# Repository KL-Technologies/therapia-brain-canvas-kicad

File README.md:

# brain_canvas_kicad

Brain Canvas Rev.A (Therapia EEG/HRV board) を **EasyEDA Pro から KiCad 10 へ移行**し、
以後のレイアウト修理・製造データ出力を KiCad 側でヘッドレスに回すためのパイプライン。

対象基板: 4層 / 61.8236 × 45.0088 mm (2434 × 1772 mil) / 部品 131 個・全数 Top 実装。

## 前提

| 名前 | パス | 用途 |
|---|---|---|
| `KC` | `/Applications/KiCad/KiCad.app/Contents/MacOS/kicad-cli` | DRC・Gerber 等の CLI（10.0.5） |
| `KPY` | `/Applications/KiCad/KiCad.app/Contents/Frameworks/Python.framework/Versions/Current/bin/python3` | `pcbnew` を持つ Python（3.9.13） |
| system `python3` | `/usr/bin/python3`（3.9.6） | 純 JSON 処理のステップ |

環境変数 `KC` / `KPY` で上書きできる。スクリプトは**標準ライブラリのみ**・**冪等**（再実行しても同じ結果）。
GUI は一切使わない。

## 使い方

```sh
./run.sh              # 未完のステップから順に実行（ゲート pass 済みは飛ばす）
./run.sh --status     # ゲート一覧を表示するだけ
./run.sh --force      # S0 から全部やり直す
./run.sh --from S2    # 指定ステップから再実行
./run.sh --no-commit  # git commit を作らない
```

ゲートが落ちると `exit 1` で停止する。**S1 の失敗は「.epro がまだ無い」待ち状態**であって
不具合ではない（`STATUS.md` 参照）。各ステップ成功後に `git commit` が入る。

```sh
python3 scripts/99_selftest.py   # 合成 .epro でパーサ／パッチャの動作確認（KiCad 不要）
```

## ステップ

| ID | スクリプト | 実行系 | 内容 | ゲート |
|---|---|---|---|---|
| S0 | `scripts/00_env_check.sh` | bash | kicad-cli / pcbnew / `EASYEDAPRO` / `ZONE_FILLER` / `drc --refill-zones` の存在確認 | `gates/S0.json` |
| S1 | `scripts/05_find_epro.sh` | bash + python3 | `~/Downloads` `~/Desktop` `~/Documents` `therapia-device/` から `.epro` / `.epro2` を捜して `import/` へ複製し sha256 記録 | `gates/S1.json` |
| S1B | `scripts/06_epro2_to_epro.py` | python3 | `.epro2`（EasyEDA Pro 3.2）を KiCad が読める旧 `.epro` へ変換。旧形式が既にあれば何もしない | `gates/S1B.json` |
| S2 | `scripts/10_epro_inventory.py` | python3 | `.epro` を自前パースして EasyEDA 側の員数表を作る | `gates/inventory_easyeda.json` |
| S2 | `scripts/11_import_epro.py` | KPY | パッチ段階を変えながら `PCB_IO_MGR.Load(EASYEDAPRO)` → `Save(KICAD_SEXP)` → パッド網の補修 → DRC | `board/*.kicad_pcb` |
| S2 | `scripts/12_verify_import.py` | KPY | `pcbnew.LoadBoard` で読み直して EasyEDA 側と突合 | `gates/S2.json` |
| S2B | `scripts/20_netlist_contract.py` | python3 | 回路図ネットリスト TSV を契約化し、PCB との差分（＝ECO-1 の残作業）を列挙 | `gates/S2B.json` |
| S4a | `scripts/13_fix_import.py` | KPY | NPTH 6 穴を合成（M2 ×4・USB-C ペグ ×2）し、開いていた基板外形を閉じる | `gates/S4a.json` |
| S3 | `scripts/14_make_rules.py` | python3 | JLC 4 層ルールを `.kicad_pro` / `.kicad_dru` / `.kicad_pcb` の `(setup)` へ生成 | — |
| S3 | `scripts/15_gate_s3.py` | python3 + KC | DRC ベースラインを取り、**ルールが L1〜L4 を実際に検出することを検定** | `gates/S3.json` |
| S4 | `scripts/19_make_parts_table.py` | python3 | 旧 BOM ＋ ECO-2/3 の置換表から `data/parts_lcsc.csv`（135 行）を生成 | — |
| S4 | `scripts/20_apply_eco.py` | KPY + KC | ECO-1/2/3 を PCB へ適用し、契約と全パッド突合、ゾーン再充填して DRC | `gates/S4.json` |
| S5_uuids | `scripts/26_fix_uuids.py` | python3 (+KPY) | 重複 KIID 2,625 個を採番し直す。**これより前の DRC レポートはアイテムの同定が信用できない** | `gates/S5_uuids.json` |
| S5_L1 | `scripts/30_repair_L1.py` | KPY + KC | AMS1117 を取付穴 H4 から退避させ、4 ピンを繋ぎ直す | `gates/S5_L1.json` |
| S5_L2 | `scripts/31_repair_L2.py` | KPY + KC | CHASSIS_GND を H1 の外へ引き直す | `gates/S5_L2.json` |
| S5_L3 | `scripts/32_repair_L3.py` | KPY + KC | ESP_TXD を分割し、H4 に掛かる中央だけ引き直す | `gates/S5_L3.json` |
| S5_L4 | `scripts/33_repair_L4.py` | KPY + KC | USB-C ペグ穴 PEG1/PEG2 を空け、J1 の GND ランドを詰める | `gates/S5_L4.json` |
| S5_L5 | `scripts/34_repair_L5.py` | KPY + KC | 残りの近接を幾何から洗い出して解消 | `gates/S5_L5.json` |
| S5_mask | `scripts/35_mask_bridges.py` | KPY + KC | 合体したレジスト開口をパッド個別マージンで分ける | `gates/S5_mask.json` |
| S6 | `scripts/40_drc_loop.py` | python3 + KPY + KC | DRC → 修正 → DRC を clean になるまで反復 | `gates/S6.json` |
| S7a | `scripts/45_apply_eco5_and_bom.py` | KPY + KC | ECO-5（`C_BIAS_INV` pad2 を GND → BIAS_OUT_INT）と BOM 修正・DNP 2 点を反映 | `gates/S7a.json` |
| S7b | `scripts/46_analog_untouched.py` | KPY | 取り込み直後の基板とアナログ 40 ネットを突合し、差分の由来を記録から特定 | `gates/S7b.json` |
| S7c | `scripts/48_improve_vcap3.py` → `47_layout_quality.py` | KPY | バイパス C を「より近く・ビア無し」の位置へ移せるか試し、ADS1299 チェックリスト J1〜J11 を実測 | `gates/S7c.json` |
| S8 | `scripts/43_fix_pth_mask.py` → `49_normalize_layer_names.py` → `60_export_fab.sh` → `61_make_bom_cpl.py` → `63_gate_s8.py` | KPY + KC + python3 | PTH のレジスト開口を復旧し、レイヤ名を正規化してから Gerber・ドリル・BOM・CPL・プレビューを出力し、**自前パーサ**で検査 | `gates/S8.json` |
| S7 | `scripts/50_final_check.py` | KPY + KC | **ACCEPTANCE A〜G を 32 項目で判定** | `gates/S7.json` |

**S8 が S7 より先なのも意図的**。ACCEPTANCE の D〜G は S8 が出力した製造データを
読むので、先に出力しないと最終ゲートに検査対象が無い。

**S4a が S3 より先なのは意図的**。取付穴が NPTH になるまで hole clearance ルールに
引っかかる穴が存在せず、S3 のゲート（L1/L2/L4 の検出）が成立しないため。

**S5_uuids が L1 より先なのも意図的**。KiCad の DRC は違反アイテムを KIID で保存して
レポート時に引き直すので、KIID が重複していると**別の部品を名指しする**。
取り込み直後の基板は 231 個の uuid を共有していた（1 個は 38 部品で共有）。

### 共通ライブラリ

| ファイル | 中身 |
|---|---|
| `scripts/lib/epro.py` | `.epro` のパースとパッチ、ゲート JSON の読み書き |
| `scripts/lib/route.py` | 銅箔の空間索引・衝突判定、スタブ除去、2 層ルータ（直線→L 字→via ホップ）、部品配置探索 |
| `scripts/lib/maze.py` | 2 層 A* ルータ。via 遷移つき、DRC と同じ `SHAPE::Collide` で判定し、経路は採用前に線分ごとに再検証してから直線化する。ペグ穴まわりのように「直線も L 字も via ホップも無い」場所はこれでないと通らない |
| `scripts/lib/repair.py` | S5/S6 共通。ルール値、穴までの距離、接続性（`net_components`）、修理プリミティブ（via 退避・端点退避・トラック分割迂回・穴の排除）、ゲート雛形 |
| `scripts/lib/viol.py` | DRC レポートを作業リストに変換する。ただし**位置は信用しない**（アイテム自身のアンカーが入っている） |
| `scripts/lib/drc.py` | DRC レポートの署名比較。`kicad-cli pcb drc` は同一入力で 525〜531 件と揺れるので、件数ではなく（種別, ネット集合）で比較する |
| `scripts/lib/xlsx.py` | 旧 BOM/CPL の xlsx を標準ライブラリだけで読む |
| `scripts/lib/gerber_parse.py` | RS-274X と Excellon を**自前で**読む（標準ライブラリのみ）。C/R/O/P アパーチャ、KiCad の `RoundRect` マクロ、G36/G37 リージョン、G75 円弧、LPD/LPC 極性。未知のマクロは外接円に落とす（穴クリアランス検査で銅を過大評価する側なので、誤警報は出しても見逃しは出さない）。**KiCad に自分の出力を読み直させても、自分と矛盾していないことしか分からない** — S8 の PTH レジスト欠落はこれで見つかった |

`import/` に**正規の旧 `.epro`** と `.epro2` が両方あるときは、必ず旧 `.epro` を使う（変換を挟まないぶん確実）。
`.converted.epro` は最下位。

## 落とし穴 3 つ（実測で確認済み）

### 1. `.epro2` は KiCad 10.0.5 では読めない。しかもエラーが出ない

EasyEDA Pro 3.2 の書き出しは `project2.json` ＋ 単一の `.epru`（全ドキュメントを
`{ヘッダ}||{本体}|\n` で連結したログ形式）。KiCad のバイナリに `project2.json` / `epru` /
`epro2` の文字列は 1 つも無く、`PCB_IO_MGR.Load` に渡すと **例外を出さずに空の基板
（フットプリント 0・ネット 1）を返す**。気づかず先へ進める形の失敗なので、S1 で形式を判定し
S1B で変換する。変換で運ばないもの:

- `RULE` — 3.2 の設計ルールは入れ子構造で旧形式への対応が付かない（これを誤ると #24303 を踏む）。値は `contract/easyeda_rules.json` に出すので S3 が `.kicad_pro` へ意図して書き写す
- `POURED` — EasyEDA が計算済みの銅箔充填。KiCad が `drc --refill-zones` で作り直すし、S3 は編集後にどのみち再充填が要る

### 2. 同じ番号のパッドは 1 つしかネットが付かない

KiCad は `PAD_NET` を `FindPadByNumber()` で当てるので、**同一番号のパッドが複数あると最初の 1 枚
にしか付かない**。この基板では ESP32 のサーマルパッド（`39` ×9）と USB-C のシェル脚
（`13`/`14` ×2）が該当し、GND が 10 パッド落ちる。`11_import_epro.py` が取り込み後に
EasyEDA 側の表を全パッドへ再適用して直す（`logs/pad_net_repair.json`）。

### 3. `kicad-cli pcb drc` はコマンドサンドボックス内では動かない（かつ非決定的）

サンドボックス下では `Swift/SwiftNativeNSArray.swift:78: Fatal error: Array index out of range`
で落ちる（Swift のエラーは表面的な症状で、原因は macOS のサービスが塞がれていること）。
`export gerbers` などほかのサブコマンドは影響を受けない。**DRC はサンドボックス外で実行する。**
通常のターミナルからは普通に動く。

さらに **DRC の出力は同一の基板に対しても揺れる**。実測で 525 / 528 / 531 件。
同じ物理的問題を代表する要素の選ばれ方が変わるためで、たとえば

```
run A   Track [V_NLDO_IN] on Bottom Layer, length 2.2860 mm  <-> Via [VNEG5]
run B   Track [V_NLDO_IN] on Bottom Layer, length 0.2543 mm  <-> Via [VNEG5]
```

は同じ 1 箇所を指している。したがって**件数で合否を判定してはいけない**。
`scripts/lib/drc.py` の署名（種別 ＋ ネット集合）で比較する。
部品参照を署名に含めてはいけない ── track（部品名を含まない）と pad（含む）が
入れ替わるだけで、無変更の基板が「新規 10 件・解決 10 件」に見える。

### 4. KIID は一意ではない（この基板では 231 個が重複）

EasyEDA インポータがライブラリ部品の全インスタンスに同じ KIID を振る。実測で
**38 個の部品が 1 個の uuid を共有し、その 38 個の 1 番パッドがまた別の 1 個を共有**。
KiCad は uuid の一意性を前提にしていて、`BOARD::GetItem(KIID)` は最初に見つけた
ものを返す。

これが効いてくるのは **DRC レポート**で、KiCad は違反アイテムをポインタではなく
KIID で保存し、レポートを書くときに引き直す。重複があるとレポートは
**実在しない組み合わせを名指しする** ── 9.3 mm 離れたパッド同士の
`solder_mask_bridge`、8.9 mm 離れたパッド同士の 0.0420 mm `clearance` など。
**種別と件数は常に正しく、間違うのはアイテムの同定だけ。**

`scripts/26_fix_uuids.py` が重複を採番し直す（`.kicad_pcb` は uuid を相互参照
しないので安全。基板の幾何とネットが不変であることを検証してから保存する）。
**取り込みからやり直す場合は L1 より先にこれを通すこと。**

### 5. pcbnew の SWIG プロキシは `id()` で比較できない

基板から同じパッドを 2 回取り出すと別のプロキシが返り、`id()` が一致しない。
無視リストや訪問済み集合は `scripts/lib/route.uid()` で持つこと
（KIID 単独では上記のとおり一意でないので、パッドと部品は reference と
フットプリント相対座標を足した鍵になっている）。関連して:

- `board.Remove()` は board 直下の要素に使うと以後 `GetFootprints()` が生の
  `SwigPyObject` を返すようになる。**`RemoveNative()` を使う**
- `pcbnew.FOOTPRINT(src)` は KIID ごと複製する（複製先のパッドが元と同じ uuid を持つ）。
  `m_Uuid` は書き込み不可で `FixUuids()` も効かないので、新規部品はゼロから組み立てる
- 同一プロセスでの 2 回目の `LoadBoard`、および `SaveBoard` の後は基板を走査できない。
  計測は保存前に済ませる

## KiCad 側インポータの既知バグと回避

`.epro` は ZIP の中に JSON Lines 文書（`project.json` / `*.epcb` / `*.esch` / `*.esym` / `*.efoo`）が入る形式
（仕様: <https://dev-docs.kicad.org/en/import-formats/easyeda/index.html>）。
KiCad 10 のインポータは現行の EasyEDA 出力に対して 2 つ落とし穴がある。

| KiCad issue | 症状 | 回避 |
|---|---|---|
| #24303 | パースが `type must be number, but is array` で落ちる。EasyEDA 2.2+ の `RULE` レコードが payload を 1 段深い dict に入れるため | `RULE` の `ruleData` を旧形式へ平坦化（clearance=`ruleType "1"` / track width=`"3"`） |
| #19021 | 読み込みは成功するのに**全パッド・全トラックが 1 ネットに融合**する。新しい出力が先頭の `NET` 宣言を落とすため | 各プリミティブの net 名フィールドを走査して、未宣言のネットを `["NET", name]` としてヘッダ直後に再注入 |
| （併発） | `std::out_of_range: map::at` で落ちる | 文書内の CRLF を LF へ正規化 |

手法は <https://github.com/enkhbold470/epro2kicad> を参照して `scripts/lib/epro.py` に自前実装した
（外部依存としては入れていない）。`11_import_epro.py` は

`raw` → `newlines` → `newlines+rules` → `newlines+rules+nets`

の 4 段階をそれぞれ**別プロセスの KPY で**試し（パーサが abort しても子プロセスだけが死ぬ）、
`gates/inventory_easyeda.json` の員数と突き合わせて**一番手を加えていないのに員数が合う段階**を採用する。
採用結果は `logs/import_attempts.json` / `logs/import_summary.json` に残る。

## 単位と座標

- EasyEDA Pro の PCB 内部単位は **mil**、**y は下向きが負**。`mm = mil × 0.0254`。
- KiCad は内部単位 nm、**y は下向きが正**。したがって EasyEDA の点 `(x, y)` は KiCad の `(x, −y)` に対応する。
- さらに KiCad は取り込み時に基板を **(120, 80) mm** 平行移動する（実測値。`gates/S2.json` の
  `board_offset_mm` に毎回記録される）。**S3 以降で EasyEDA 由来の座標メモ
  （`11_rev_a_eco_2026-08-16.md` の L1〜L6 など）を KiCad 上で使うときは
  `kicad = (x + 120, −y + 80)` [mm] で読み替えること。**
- 部品ローカル座標 → 基板座標は単純な回転（軸反転なし）:
  `bx = cx + lx·cosθ − ly·sinθ` / `by = cy + lx·sinθ + ly·cosθ`。
  `10_epro_inventory.py` が毎回 131 部品分を `fab_2026-08-16` の CPL（Pad X/Pad Y）と突き合わせて
  検証する（`cpl_crosscheck.placement_transform_verified`）。

## ディレクトリ

```
import/    .epro 原本（SHA256SUMS 付き）と patched.epro
board/     KiCad 成果物 (.kicad_pcb / .kicad_pro)
scripts/   パイプライン本体（lib/ は共通パーサ）
gates/     各ステップの合否 JSON と員数表
contract/  ネットリスト（S3 の契約）
fab/       製造データ（S8）。zip・BOM・CPL・プレビュー・実装図・README_発注手順.md
logs/      実行ログ・DRC 出力・パッチ試行履歴
```

## 参照する既存資料（読むだけ・変更しない）

- `../cerelog_research/11_rev_a_eco_2026-08-16.md` — ECO-1〜3 とレイアウト修理 L1〜L6 の正本
- `../cerelog_research/PROJECT_STATUS.md` — 経緯・ネット員数の記録
- `../cerelog_research/fab_2026-08-16/` — 旧版の Gerber / BOM / CPL。CPL の 131 designator と
  回転角は S2 の独立参照として自動で突合される

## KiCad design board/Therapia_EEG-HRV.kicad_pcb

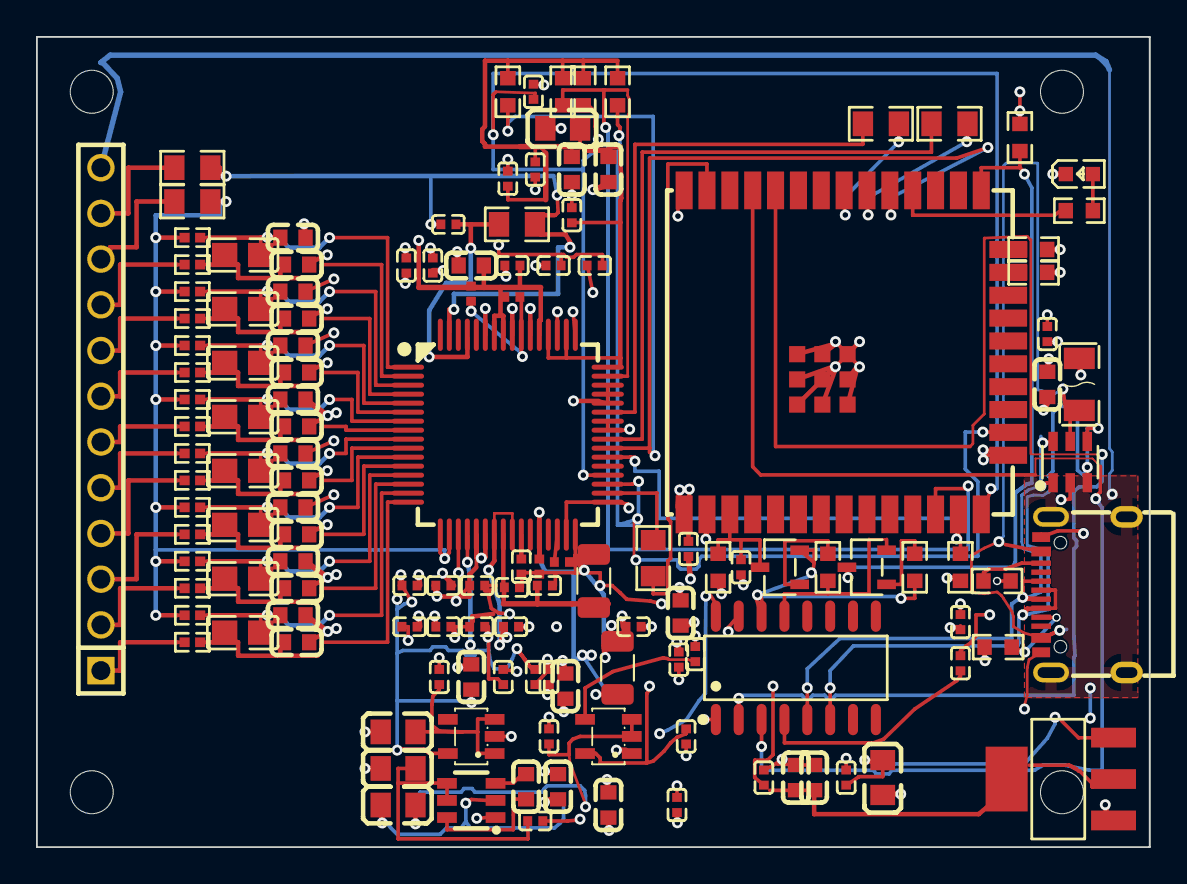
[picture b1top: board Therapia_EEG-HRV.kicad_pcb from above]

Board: 4 copper layers, 61.8 x 45.0 mm, 141 parts (0 on the bottom side), 79 nets.

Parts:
AMS1117: AMS1117-3.3; SOT-223-3_L6.5-W3.4-P2.30-LS7.0-BR
C_3V3_B, C_3V3_B2, C_3V3_OUT: 10uF; C0603
C_3V3_H, C_3V3_H2: 100nF; C0402
C_3V3_IN, C_3V3_M: 1uF; C0402
C_AVDD1_1u: 1uF; C0402
C_AVDD1_10n: 10nF 50V X7R 0402; C0402
C_AVDD1_10u: 10uF; C0603
C_AVDD1_100n: 100nF; C0402
C_AVDD_B: 10uF; C0603
C_AVDD_H: 100nF; C0402
C_AVDD_P3, C_AVDD_P19, C_AVDD_P31, C_AVDD_P36, C_AVDD_P64: 100nF; C0402
C_AVDD_P59: 1uF; C0402
C_AVSS_B: 10uF; C0603
C_AVSS_H: 100nF; C0402
C_AVSS_P17, C_AVSS_P30, C_AVSS_P37, C_AVSS_P60: 100nF; C0402
C_BIAS_INV: 1.5nF 50V X7R 0402; C0402
C_BULK: 10uF; C0603
C_CM1N, C_CM1P, C_CM2N, C_CM2P, C_CM3N, C_CM3P, C_CM4N, C_CM4P, C_CM5N, C_CM5P, C_CM6N, C_CM6P, C_CM7N, C_CM7P, C_CM8N, C_CM8P: 1nF 50V C0G 0603; C0603
C_DIF1, C_DIF2, C_DIF3, C_DIF4, C_DIF5, C_DIF6, C_DIF7, C_DIF8: 10nF_NP0_50V; C0805
C_DVDD_10u: 10uF; C0603
C_DVDD_B: 10uF; C0603
C_DVDD_H: 100nF; C0402
C_DVDD_P40, C_DVDD_P58: 100nF; C0402
C_EN_DLY: 1uF 0402; C0402
C_HF: 100nF; C0402
C_LM_FLY: 10uF; C0603
C_LM_IN: 4.7uF 10V X5R 0402; C0402
C_LM_OUT: 10uF; C0603
C_NLDO_IN: 1uF; C0402
C_NLDO_OUT: 4.7uF 10V X5R 0402; C0402
C_NR: 10nF; C0402
C_PLDO_IN: 1uF; C0402
C_PLDO_OUT: 1uF; C0402
C_RST_DLY: 100nF; C0402
C_USB5V_B: 10uF; C0603
C_USB5V_H: 100nF; C0402
C_USB_V3: 100nF; C0402
C_USB_VCC: 100nF; C0402
C_VCAP1: 100uF; C_1206_3216Metric
C_VCAP1_H, C_VCAP3_H: 100nF; C0402
C_VCAP2, C_VCAP3, C_VCAP4: 1uF; C0402
C_VREFP_10n: 10nF 50V X7R 0402; C0402
C_VREFP_10u: 10uF 50V X5R 1206; C_1206_3216Metric
C_VREFP_100n: 100nF; C0402
D_ESD: USBLC6-2SC6; SOT-23-6_L2.9-W1.6-P0.95-LS2.8-BL
D_LED: LED yellow 0603 Vf1.6-2.6V; LED0603-RD
F1: PTC 0.5A hold / 1A trip / 13.2V 1206; F1206
FB1, FB2, FB3, FB4, FB5: 600R@100MHz 0805; L0805
H1: NPTH_2.3876mm_M2; Pad_e525
H2: NPTH_2.3876mm_M2; Pad_e526
H3: NPTH_2.3876mm_M2; Pad_e527
H4: NPTH_2.3876mm_M2; Pad_e528
J1: USB-C_16P; USB-C-SMD_TYPE-C-6PIN-2MD-073
J2: Header_2x6; HDR-TH_12P-P2.54-V-M
LM2664: LM2664; SOT-23-6_L2.9-W1.6-P0.95-LS2.8-BR
PEG1, PEG2: NPTH_0.7000mm_peg; NPTH_0.7mm_USB-C_peg
Q_EN: S8050; SOT-23-3_L3.0-W1.7-P0.95-LS2.9-BR
Q_IO0: S8050; SOT-23-3_L3.0-W1.7-P0.95-LS2.9-BR
R_BIAS_FB: 1M; R0805
R_BIAS_SER: 1M; R0805
R_CC1, R_CC2: 5.1k; R0603
R_CS_UP: 10k; R0603
R_DRDY_UP: 10k; R0603
R_EN_UP: 10k; R0603
R_IN1N, R_IN1P, R_IN2N, R_IN2P, R_IN3N, R_IN3P, R_IN4N, R_IN4P, R_IN5N, R_IN5P, R_IN6N, R_IN6P, R_IN7N, R_IN7P, R_IN8N, R_IN8P: 10k; R0402
R_IO0_UP, R_IO2_DN, R_IO15_DN: 10k; R0603
R_LED: 330R; R0603
R_MISO: 0R; R0805
R_MOSI: 0R; R0805
R_PWDN_UP: 10k; R0603
R_Q_EN_B: 470k; R0603
R_Q_IO0_B: 470k; R0603
R_RST_UP: 10k; R0603
R_SCLK: 0R; R0805
R_SRB_SER: 0R; R0805
R_START_DN: 10k; R0603
TLV70025: TLV70025; SOT-23-5_L3.0-W1.7-P0.95-LS2.8-BR
TPS72325: TPS72325; SOT-23-5_L3.0-W1.7-P0.95-LS2.8-BR
U_ADS: ADS1299; TQFP-64_L10.0-W10.0-P0.50-LS12.0-TL
U_MCU: ESP32-WROOM-32UE-N4; WIFI-SMD_ESP32-WROOM-32E
U_USB: CH340C; SOP-16_L10.0-W3.9-P1.27-LS6.0-BL

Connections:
A1_ELEC: J2.11, R_BIAS_SER.2
A2_ELEC: J2.10, R_SRB_SER.2
ADS_CS_N: R_CS_UP.1, U_ADS.39, U_MCU.29
ADS_DIN_LOC: R_MOSI.1, U_ADS.34
ADS_DOUT_LOC: R_MISO.1, U_ADS.43
ADS_DRDY_N: R_DRDY_UP.1, U_ADS.47, U_MCU.12
ADS_PWDN_N: R_PWDN_UP.1, U_ADS.35, U_MCU.16
ADS_RESET_N: C_RST_DLY.1, R_RST_UP.1, U_ADS.36, U_MCU.14
ADS_SCLK_LOC: R_SCLK.1, U_ADS.40
ADS_START: R_START_DN.1, U_ADS.38, U_MCU.13
AVDD: C_AVDD1_1u.1, C_AVDD1_10n.1, C_AVDD1_10u.1, C_AVDD1_100n.1, C_AVDD_B.1, C_AVDD_H.1, C_AVDD_P3.1, C_AVDD_P19.1, C_AVDD_P31.1, C_AVDD_P36.1, C_AVDD_P59.1, C_AVDD_P64.1, C_PLDO_OUT.2, TLV70025.5, U_ADS.19, U_ADS.21, U_ADS.22, U_ADS.54, U_ADS.56, U_ADS.59
AVSS: C_AVDD1_1u.2, C_AVDD1_10n.2, C_AVDD1_10u.2, C_AVDD1_100n.2, C_AVSS_B.1, C_AVSS_H.1, C_AVSS_P17.1, C_AVSS_P30.1, C_AVSS_P37.1, C_AVSS_P60.1, C_NLDO_OUT.2, C_VCAP1.2, C_VCAP1_H.2, C_VCAP2.2, C_VCAP3.2, C_VCAP3_H.2, C_VCAP4.2, C_VREFP_10n.2, C_VREFP_10u.2, C_VREFP_100n.2, TPS72325.5, U_ADS.20, U_ADS.23, U_ADS.25, U_ADS.32, U_ADS.53, U_ADS.57, U_ADS.58
BIAS_INV: C_BIAS_INV.1, R_BIAS_FB.1, U_ADS.61
BIAS_OUT_INT: C_BIAS_INV.2, R_BIAS_FB.2, R_BIAS_SER.1, U_ADS.63
CH3_ELEC: J2.3, R_IN3P.1
CH5_ELEC: J2.6, R_IN5P.1
CH6_ELEC: J2.7, R_IN6P.1
CH7_ELEC: J2.8, R_IN7P.1
CH8_ELEC: J2.9, R_IN8P.1
CH340_V3: C_USB_V3.1, U_USB.4
CHASSIS_GND: J1.13, J1.14, J2.12
CH_DTR_N: Q_IO0.2, R_Q_EN_B.1, U_USB.13
CH_RTS_N: Q_EN.2, R_Q_IO0_B.1, U_USB.14
DVDD: C_DVDD_10u.1, C_DVDD_B.1, C_DVDD_H.1, C_DVDD_P40.1, C_DVDD_P58.1, FB5.2, R_CS_UP.2, R_DRDY_UP.2, R_PWDN_UP.2, R_RST_UP.2, U_ADS.48, U_ADS.50, U_ADS.52
ECGN_ELEC: J2.5, R_IN4N.1
ECGP_ELEC: J2.4, R_IN4P.1
ESP_EN: C_EN_DLY.1, Q_EN.3, R_EN_UP.2, U_MCU.3
ESP_IO0: Q_IO0.3, R_IO0_UP.2, U_MCU.25
ESP_IO2: R_IO2_DN.1, U_MCU.24
ESP_IO15: R_IO15_DN.1, U_MCU.23
ESP_RXD: U_MCU.34, U_USB.2
ESP_TXD: U_MCU.35, U_USB.3
FP1_ELEC: J2.1, R_IN1P.1
FP2_ELEC: J2.2, R_IN2P.1
GND: AMS1117.1, C_3V3_B.2, C_3V3_B2.2, C_3V3_H.2, C_3V3_H2.2, C_3V3_IN.2, C_3V3_M.2, C_3V3_OUT.2, C_AVDD_B.2, C_AVDD_H.2, C_AVDD_P3.2, C_AVDD_P19.2, C_AVDD_P31.2, C_AVDD_P36.2, C_AVDD_P59.2, C_AVDD_P64.2, C_AVSS_B.2, C_AVSS_H.2, C_AVSS_P17.2, C_AVSS_P30.2, C_AVSS_P37.2, C_AVSS_P60.2, C_BULK.2, C_CM1N.2, C_CM1P.2, C_CM2N.2, C_CM2P.2, C_CM3N.2, C_CM3P.2, C_CM4N.2, C_CM4P.2, C_CM5N.2, C_CM5P.2, C_CM6N.2, C_CM6P.2, C_CM7N.2, C_CM7P.2, C_CM8N.2, C_CM8P.2, C_DVDD_10u.2, C_DVDD_B.2, C_DVDD_H.2, C_DVDD_P40.2, C_DVDD_P58.2, C_EN_DLY.2, C_HF.2, C_LM_IN.2, C_LM_OUT.2, C_NLDO_IN.2, C_NLDO_OUT.1, C_NR.2, C_PLDO_IN.2, C_PLDO_OUT.1, C_RST_DLY.2, C_USB5V_B.2, C_USB5V_H.2, C_USB_V3.2, C_USB_VCC.2, D_ESD.2, D_LED.1, J1.1, J1.12, LM2664.1, R_CC1.2, R_CC2.2, R_IO2_DN.2, R_IO15_DN.2, R_START_DN.2, TLV70025.2, TPS72325.1, U_ADS.31, U_ADS.33, U_ADS.41, U_ADS.42, U_ADS.44, U_ADS.45, U_ADS.46, U_ADS.49, U_ADS.51, U_MCU.1, U_MCU.15, U_MCU.38, U_MCU.39, U_USB.1, U_USB.15
IN1N: C_CM1N.1, C_DIF1.2, R_IN1N.2, U_ADS.15
IN1P: C_CM1P.1, C_DIF1.1, R_IN1P.2, U_ADS.16
IN2N: C_CM2N.1, C_DIF2.2, R_IN2N.2, U_ADS.13
IN2P: C_CM2P.1, C_DIF2.1, R_IN2P.2, U_ADS.14
IN3N: C_CM3N.1, C_DIF3.2, R_IN3N.2, U_ADS.11
IN3P: C_CM3P.1, C_DIF3.1, R_IN3P.2, U_ADS.12
IN4N: C_CM4N.1, C_DIF4.2, R_IN4N.2, U_ADS.9
IN4P: C_CM4P.1, C_DIF4.1, R_IN4P.2, U_ADS.10
IN5N: C_CM5N.1, C_DIF5.2, R_IN5N.2, U_ADS.7
IN5P: C_CM5P.1, C_DIF5.1, R_IN5P.2, U_ADS.8
IN6N: C_CM6N.1, C_DIF6.2, R_IN6N.2, U_ADS.5
IN6P: C_CM6P.1, C_DIF6.1, R_IN6P.2, U_ADS.6
IN7N: C_CM7N.1, C_DIF7.2, R_IN7N.2, U_ADS.3
IN7P: C_CM7P.1, C_DIF7.1, R_IN7P.2, U_ADS.4
IN8N: C_CM8N.1, C_DIF8.2, R_IN8N.2, U_ADS.1
IN8P: C_CM8P.1, C_DIF8.1, R_IN8P.2, U_ADS.2
LED_A: D_LED.2, R_LED.2
LM_CAP_N: C_LM_FLY.2, LM2664.3
LM_CAP_P: C_LM_FLY.1, LM2664.6
Q_EN_B: Q_EN.1, R_Q_EN_B.2
Q_IO0_B: Q_IO0.1, R_Q_IO0_B.2
SPI_MISO: R_MISO.2, U_MCU.31
SPI_MOSI: R_MOSI.2, U_MCU.37
SPI_SCK: R_SCLK.2, U_MCU.30
SRB1: R_IN1N.1, R_IN2N.1, R_IN3N.1, R_IN5N.1, R_IN6N.1, R_IN7N.1, R_IN8N.1, R_SRB_SER.1, U_ADS.17, U_ADS.18
STATUS_LED_DRV: R_LED.1, U_MCU.28
TPS_NR: C_NR.1, TPS72325.4
USB_5V: C_BULK.1, C_HF.1, C_USB5V_B.1, C_USB5V_H.1, C_USB_VCC.1, F1.2, FB1.1, FB2.1, FB3.1, U_USB.16
USB_CC1: J1.4, R_CC1.1
USB_CC2: J1.10, R_CC2.1
USB_DM: D_ESD.3, D_ESD.4, J1.5, J1.7, U_USB.6
USB_DP: D_ESD.1, D_ESD.6, J1.6, J1.8, U_USB.5
USB_VBUS_RAW: D_ESD.5, F1.1, J1.2, J1.11
V5_LM_IN: C_LM_IN.1, FB1.2, LM2664.4, LM2664.5
VCAP1: C_VCAP1.1, C_VCAP1_H.1, U_ADS.28
VCAP2: C_VCAP2.1, U_ADS.30
VCAP3: C_VCAP3.1, C_VCAP3_H.1, U_ADS.55
VCAP4: C_VCAP4.1, U_ADS.26
VDD_ESP: AMS1117.2, AMS1117.4, C_3V3_B.1, C_3V3_B2.1, C_3V3_H.1, C_3V3_H2.1, C_3V3_M.1, C_3V3_OUT.1, FB5.1, R_EN_UP.1, R_IO0_UP.1, U_MCU.2
VNEG5: C_LM_OUT.1, FB4.1, LM2664.2
VREFP: C_VREFP_10n.1, C_VREFP_10u.1, C_VREFP_100n.1, U_ADS.24
V_3V3_IN: AMS1117.3, C_3V3_IN.1, FB3.2
V_NLDO_IN: C_NLDO_IN.1, FB4.2, TPS72325.2, TPS72325.3
V_PLDO_IN: C_PLDO_IN.1, FB2.2, TLV70025.1, TLV70025.3

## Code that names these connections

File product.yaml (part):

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    # the device -- a class of nets, hence prefixes.
    no_via_in_span_prefixes: [VCAP, VREF]
    # All eight channels are wired to electrodes in the contract: R_IN<n>P
    # pin 1 is FP1/FP2/CH3/ECGP/CH5-CH8_ELEC, R_IN<n>N pin 1 is SRB1 (IN4N:
    # ECGN_ELEC). SRB1 is the common reference. No channel is dead.
    live_analog_nets: [IN1P, IN1N, IN2P, IN2N, IN3P, IN3N, IN4P, IN4N,
                       IN5P, IN5N, IN6P, IN6N, IN7P, IN7N, IN8P, IN8N, SRB1]
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    spi_nets: [ADS_SCLK_LOC, ADS_DIN_LOC, ADS_DOUT_LOC, ADS_CS_N, ADS_DRDY_N]
    # the one ground plane (In1.Cu GND); 47_layout_quality.py J5 probes GND
    ground_nets: [GND]
    # AVDD1 (pin 54) and AVSS1 (pin 53) sit on AVDD and AVSS in the contract:
    # there is no separate star net and no link resistor to name.
    star_links: []
    # checklist J3/J4: VCAP1 = 100 uF (DS pin table, "Connect a 100-uF
    # capacitor to AVSS"), VREFP-VREFN >= 10 uF (DS 9.3.1.3.4);
    # docs/ads1299_layout_checklist.md lines 81 and 85.
    vcap1_ref: C_VCAP1
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    # matched against anything (unused_input_channels is empty).
    unused_input_tie_suffix: ""
    out_of_scope:
      J2: "no star net: AVDD1/AVSS1 (pins 54/53) are on AVDD/AVSS in the contract, with no link resistor for a star_links triple to name"
      J7: "no unused analog input: all eight channels are wired to electrodes"
  esp32-straps:
    mcu_ref: U_MCU
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    known_defects:
      - [L1, mounting hole H4 through the AMS1117 GND pad, [hole_clearance], [NPTH pad of H4, of AMS1117]]
      - [L2, CHASSIS_GND bottom track through mounting hole H1, [hole_clearance], [NPTH pad of H1, "[CHASSIS_GND]"]]
      - [L3, ESP_TXD bottom track clipping mounting hole H4, [hole_clearance], [NPTH pad of H4, "[ESP_TXD]"]]
      - [L4a, USB_VBUS_RAW routing inside a USB-C peg hole, [hole_clearance], [NPTH pad of PEG, "[USB_VBUS_RAW]"]]
      - [L4b, a via drill overlapping a USB-C peg drill, [hole_to_hole], [NPTH pad of PEG, "Via [USB_VBUS_RAW]"]]
  S7_body:
    gap_mm: 0.15
provenance:
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
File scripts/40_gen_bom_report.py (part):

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        board_pad_geometry="pad1/pad2 とも 0.8x0.8mm 角、x=-0.749 / +0.749mm（0603 ランド）",
        board_polarity="pad1 = C（カソード）→ GND / pad2 = A（アノード）→ LED_A",
        board_polarity_source=("contract/netlist_easyeda_api_2026-08-28.tsv の "
                               "D_LED 行が pinName を保持: `D_LED 1 C GND` / `D_LED 2 A LED_A`"),
        first_choice="C72044",
        second_choice="C72038",
        rejected=["C2286", "C183844"],
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    w("- **ECO-1 は PCB に反映済み（再確認して訂正）**: 本レポート初版では"
      "「TPS72325 の pin3(EN) が `GND` のままで B1 致命バグが残存」と書いたが、"
      "これは 13:45 のネットリストに基づく古い所見だった。"
      "現在の基板ファイルでは **pin3 = `V_NLDO_IN`**（pin1=GND / pin2=V_NLDO_IN / "
      "pin4=TPS_NR / pin5=AVSS）で、ECO-1#1 は適用済み。")
    w("- **ECO-1/ECO-3 の新設・変更部品も配置済み（同上）**: `C_VCAP1_H`(VCAP1-AVSS)、"
      "`C_VCAP2`(VCAP2-AVSS)、`C_VCAP3`(VCAP3-AVSS)、`C_VCAP3_H`(VCAP3-AVSS) の 4 点が "
      "`C0402` で配置・結線済み。`C_VCAP1` と `C_VREFP_10u` も `C_1206_3216Metric` に"
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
